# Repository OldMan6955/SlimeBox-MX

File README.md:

# SlimeBox-MX
Button Box Fightstick for Toxic Players only

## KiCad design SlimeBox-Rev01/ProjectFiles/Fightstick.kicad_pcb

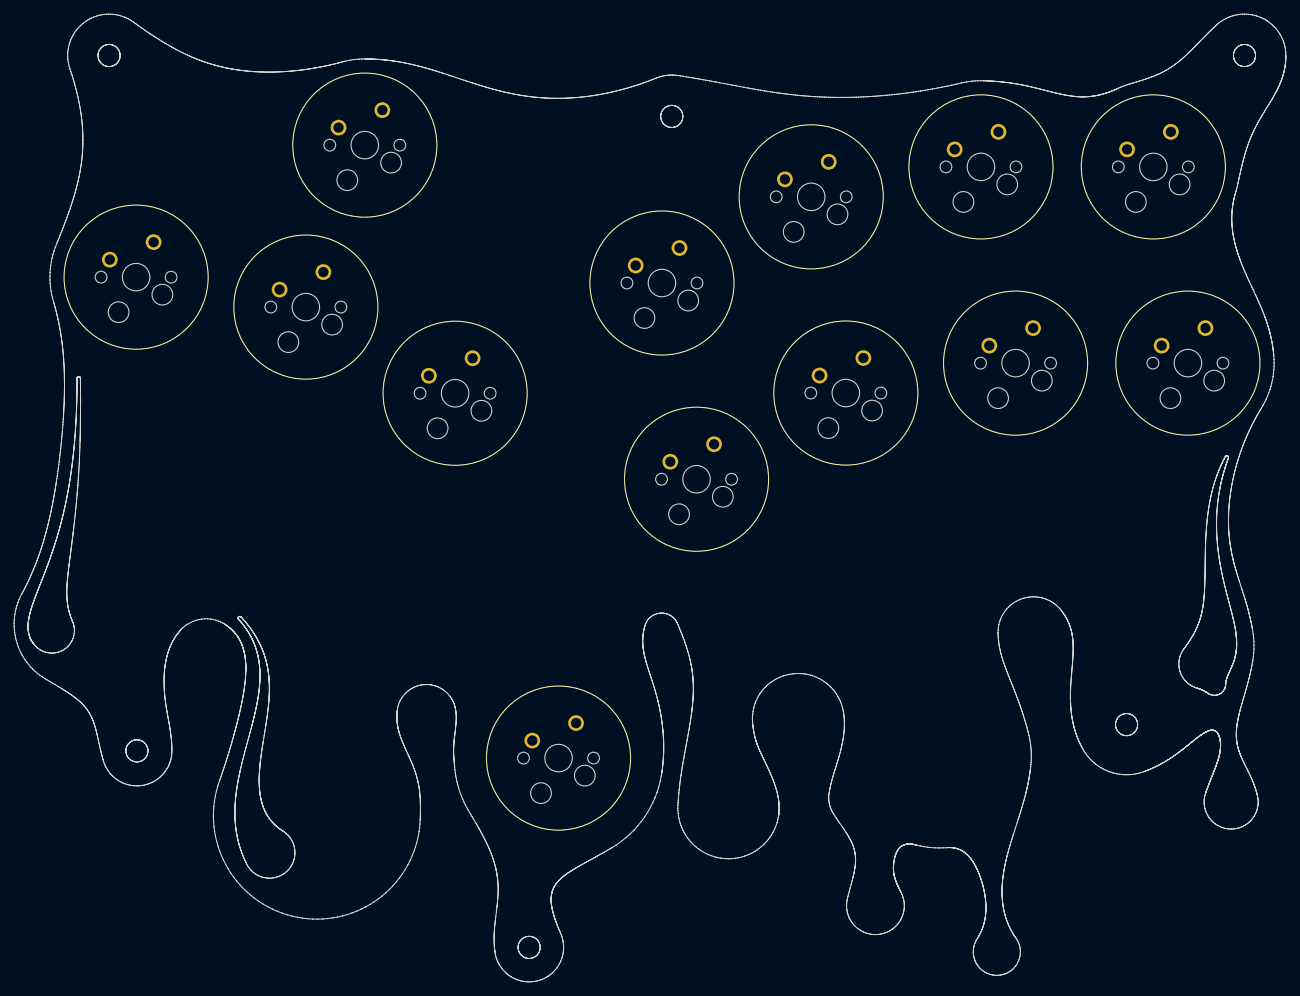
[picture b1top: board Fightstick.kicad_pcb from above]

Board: 2 copper layers, 184.5 x 140.4 mm, 14 parts (1 on the bottom side), 13 nets, no tracks yet.

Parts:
A1: RP2040-Zero
SW7, SW8, SW9, SW10, SW12, SW13, SW14, SW15, SW16, SW17, SW18, SW19: SW_Push; Kailh_socket_MX_Solder x HS Arcade Keycap 20.9
SW11: SW_Push; Kailh_socket_MX_Solder x HS Arcade Keycap 26.15

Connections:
CIRCLE: A1.8 (GPIO7), SW15.1
CROSS: A1.10 (GPIO9), SW12.1
DOWN: A1.13 (GPIO12), SW9.1
GND: A1.23 (GND), SW7.2, SW8.2, SW9.2, SW10.2, SW11.2, SW12.2, SW13.2, SW14.2, SW15.2, SW16.2, SW17.2, SW18.2, SW19.2
L1: A1.3 (GPIO2), SW17.1
L2: A1.4 (GPIO3), SW18.1
LEFT: A1.14 (GPIO13), SW7.1
R1: A1.5 (GPIO4), SW16.1
R2: A1.6 (GPIO5), SW19.1
RIGHT: A1.12 (GPIO11), SW10.1
SQUARE: A1.9 (GPIO8), SW13.1
TRIANGLE: A1.7 (GPIO6), SW14.1
UP: A1.11 (GPIO10), SW8.1, SW11.1
